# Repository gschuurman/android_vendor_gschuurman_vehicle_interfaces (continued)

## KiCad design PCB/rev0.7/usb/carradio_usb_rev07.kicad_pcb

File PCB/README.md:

# Peripheral board (mainboard)

This is the board that connects the VIM3 and the Raspberry Pi Pico 2 (vehicle MCU, firmware in `../mcu`)
to the car through the ISO 10487 harness. It also carries the audio DACs, GNSS, the display adapter, the
USB hub and the 5V supply.

- `rev0.7/` is the newest set of modules: the audio module with the car mic input (`audio/`, 2x PCM5102A + PCM1808),
  the USB module and the camera capture module (`capture_1cam/`, `capture_2cam/`). The main and GNSS boards stay at rev 0.6.
  Each folder has a README with the ordering and soldering notes.
- `rev0.6/` is the built and bench-tested main board, USB module and GNSS module, plus `stencil_jig/`.
- `rev0.5/` and `rev0.4/` are the earlier split versions (main board plus plug-in modules).
- `rev0.3/` is the single board with the RP2350B chip on it instead of the Pico 2 module.
  Read `DESIGN_rev03.md` for the changes, the 48-GPIO map and the RP2350-E9 check.
- `rev0.2/` is the Pico 2 version, and its documents still describe everything rev 0.3 didn't change.
  Start with `PCB_SUMMARY_rev02.md`, then read:
  - `DESIGN_rev02.md` for the pin map and design notes
  - `DESIGN_REVIEW_rev02.md` for the design check and layout rules
  - `ORDERING_rev02.md` for LCSC parts, cost and what to check before ordering
- `rev0.1/` is the first draft, kept for reference.
- `AUDIO.md` is the audio output plan.

The schematics are generated KiCad 7 files, for import into EasyEDA Pro. To regenerate one, run
`python3 gen3.py` inside `rev0.3/` (or `gen2.py` inside `rev0.2/`).

Rev 0.3 and later are laid out in KiCad (open with KiCad 10).

## Bring-up wizards

Each board of rev 0.6 and rev 0.7 has a step-by-step bench wizard (`WIZARD.html`) next to its design. See `wizard/README.md`.

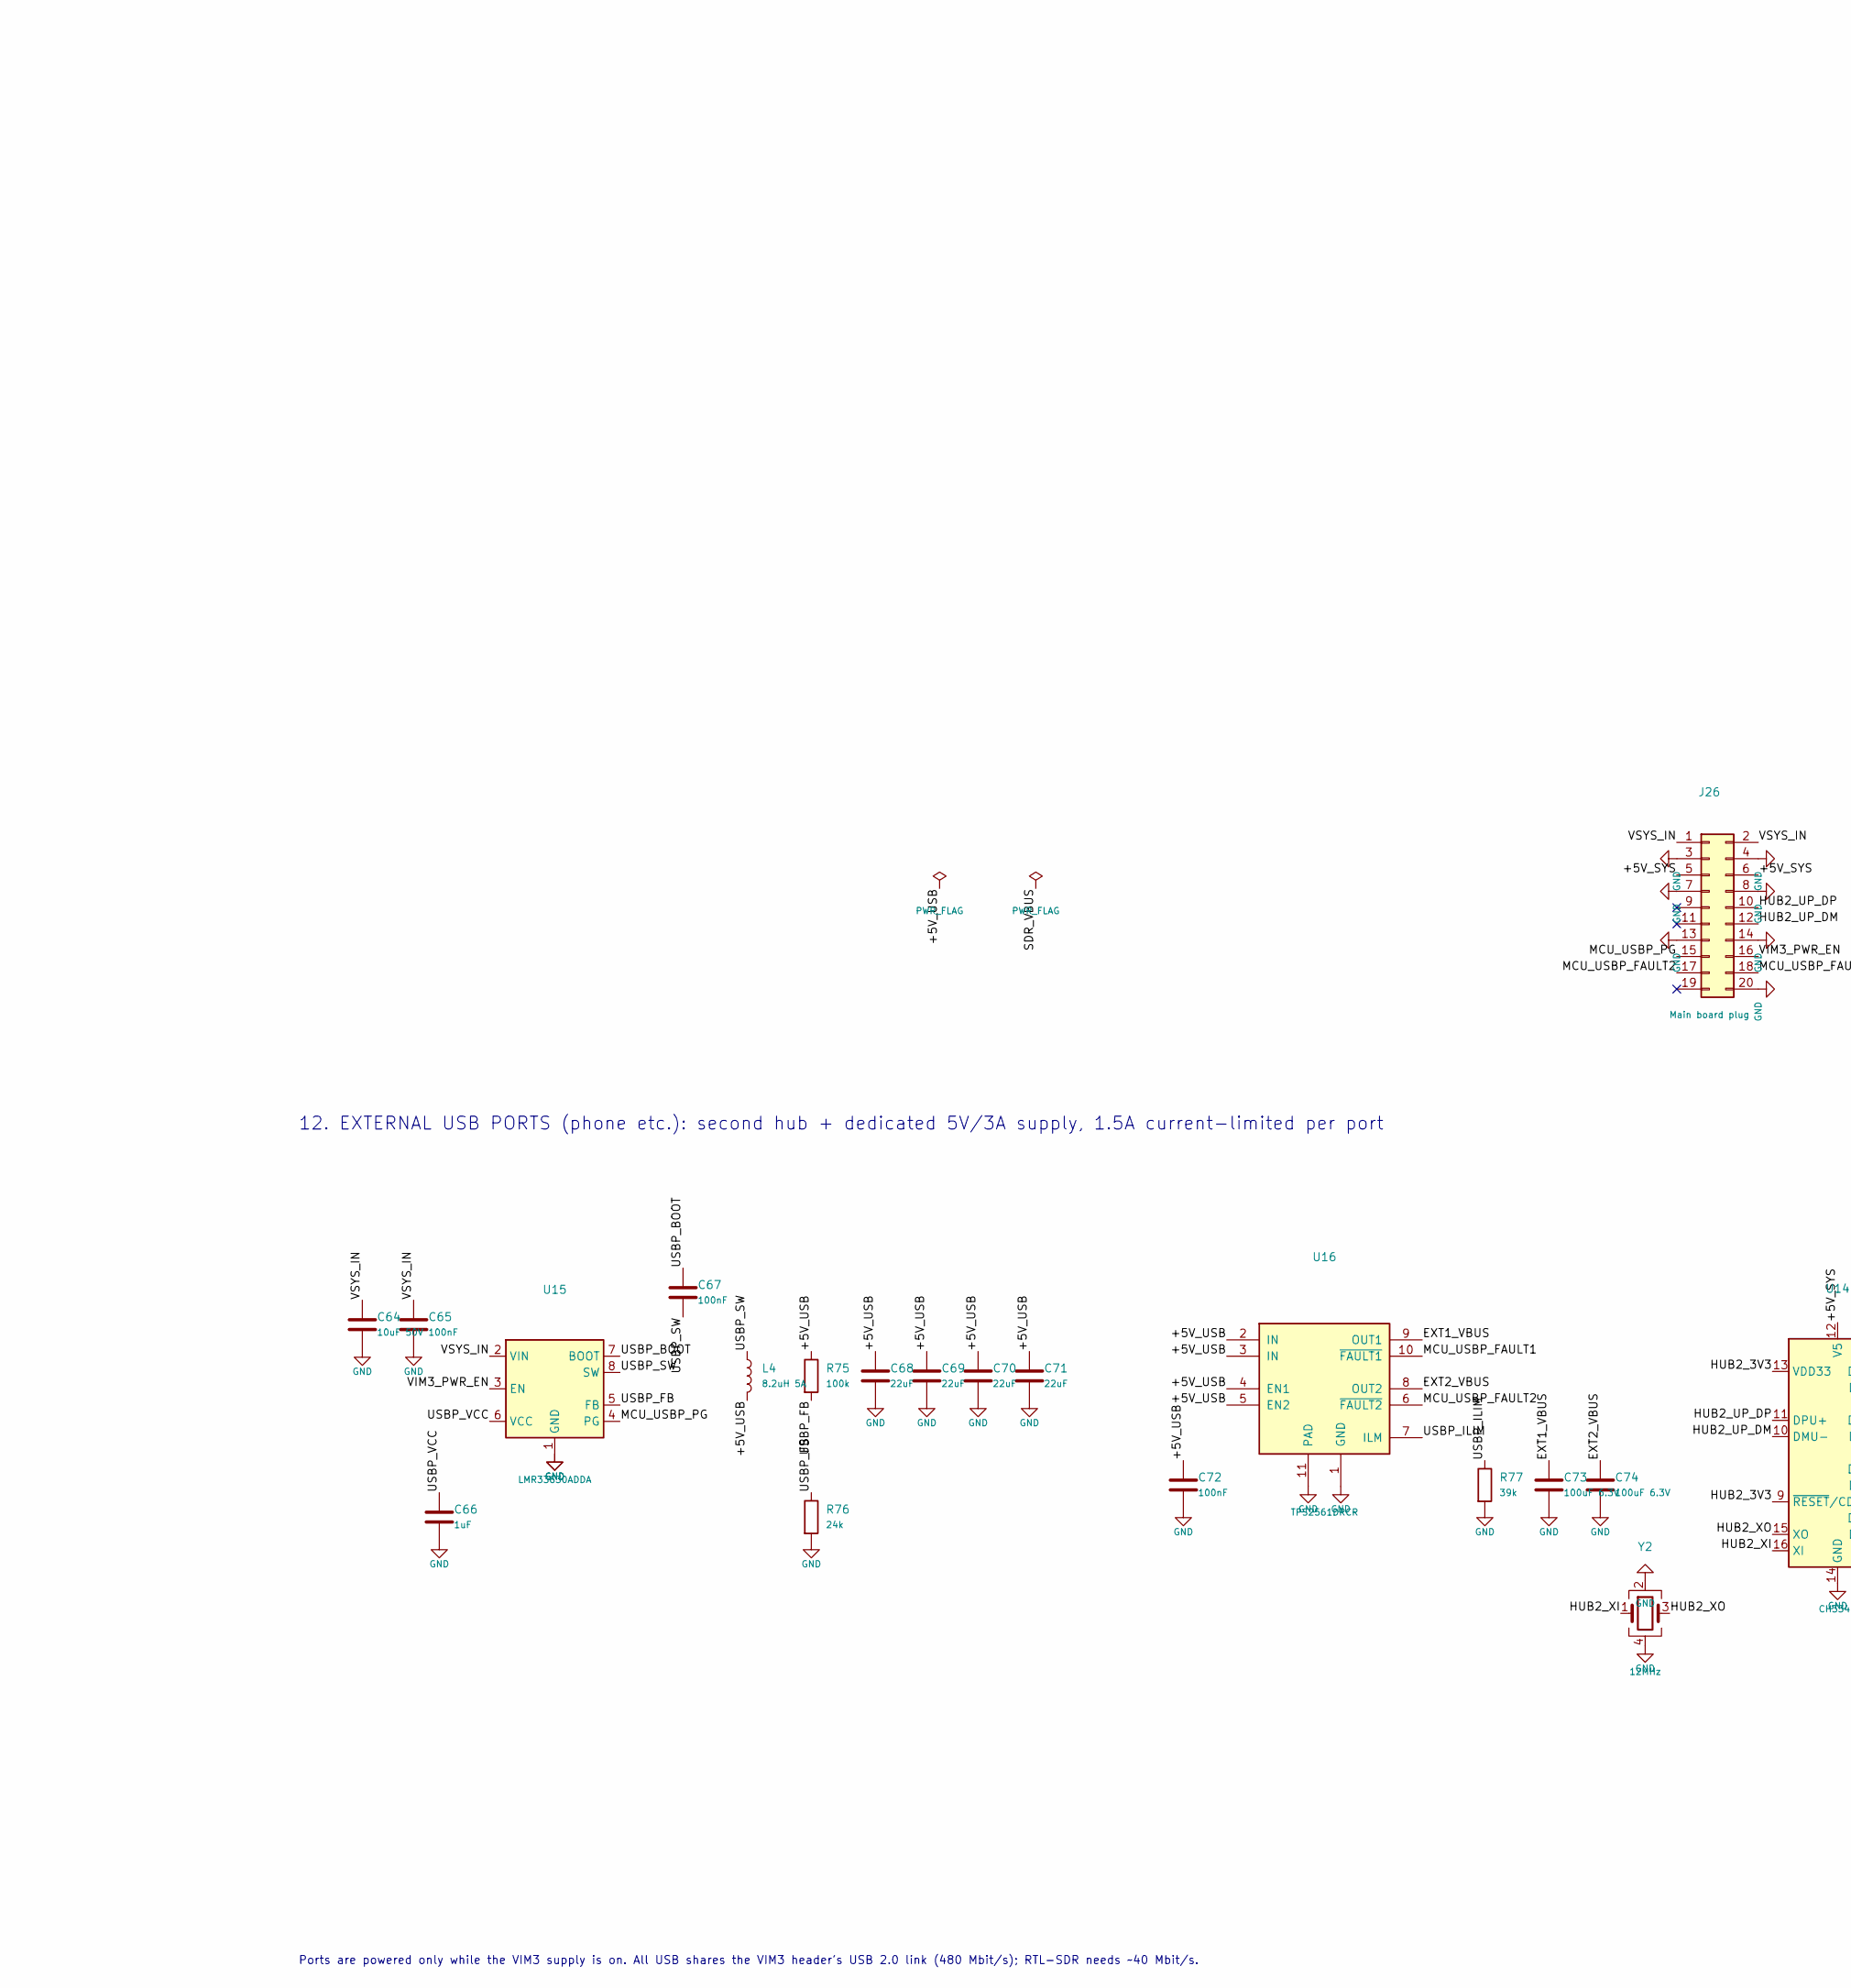
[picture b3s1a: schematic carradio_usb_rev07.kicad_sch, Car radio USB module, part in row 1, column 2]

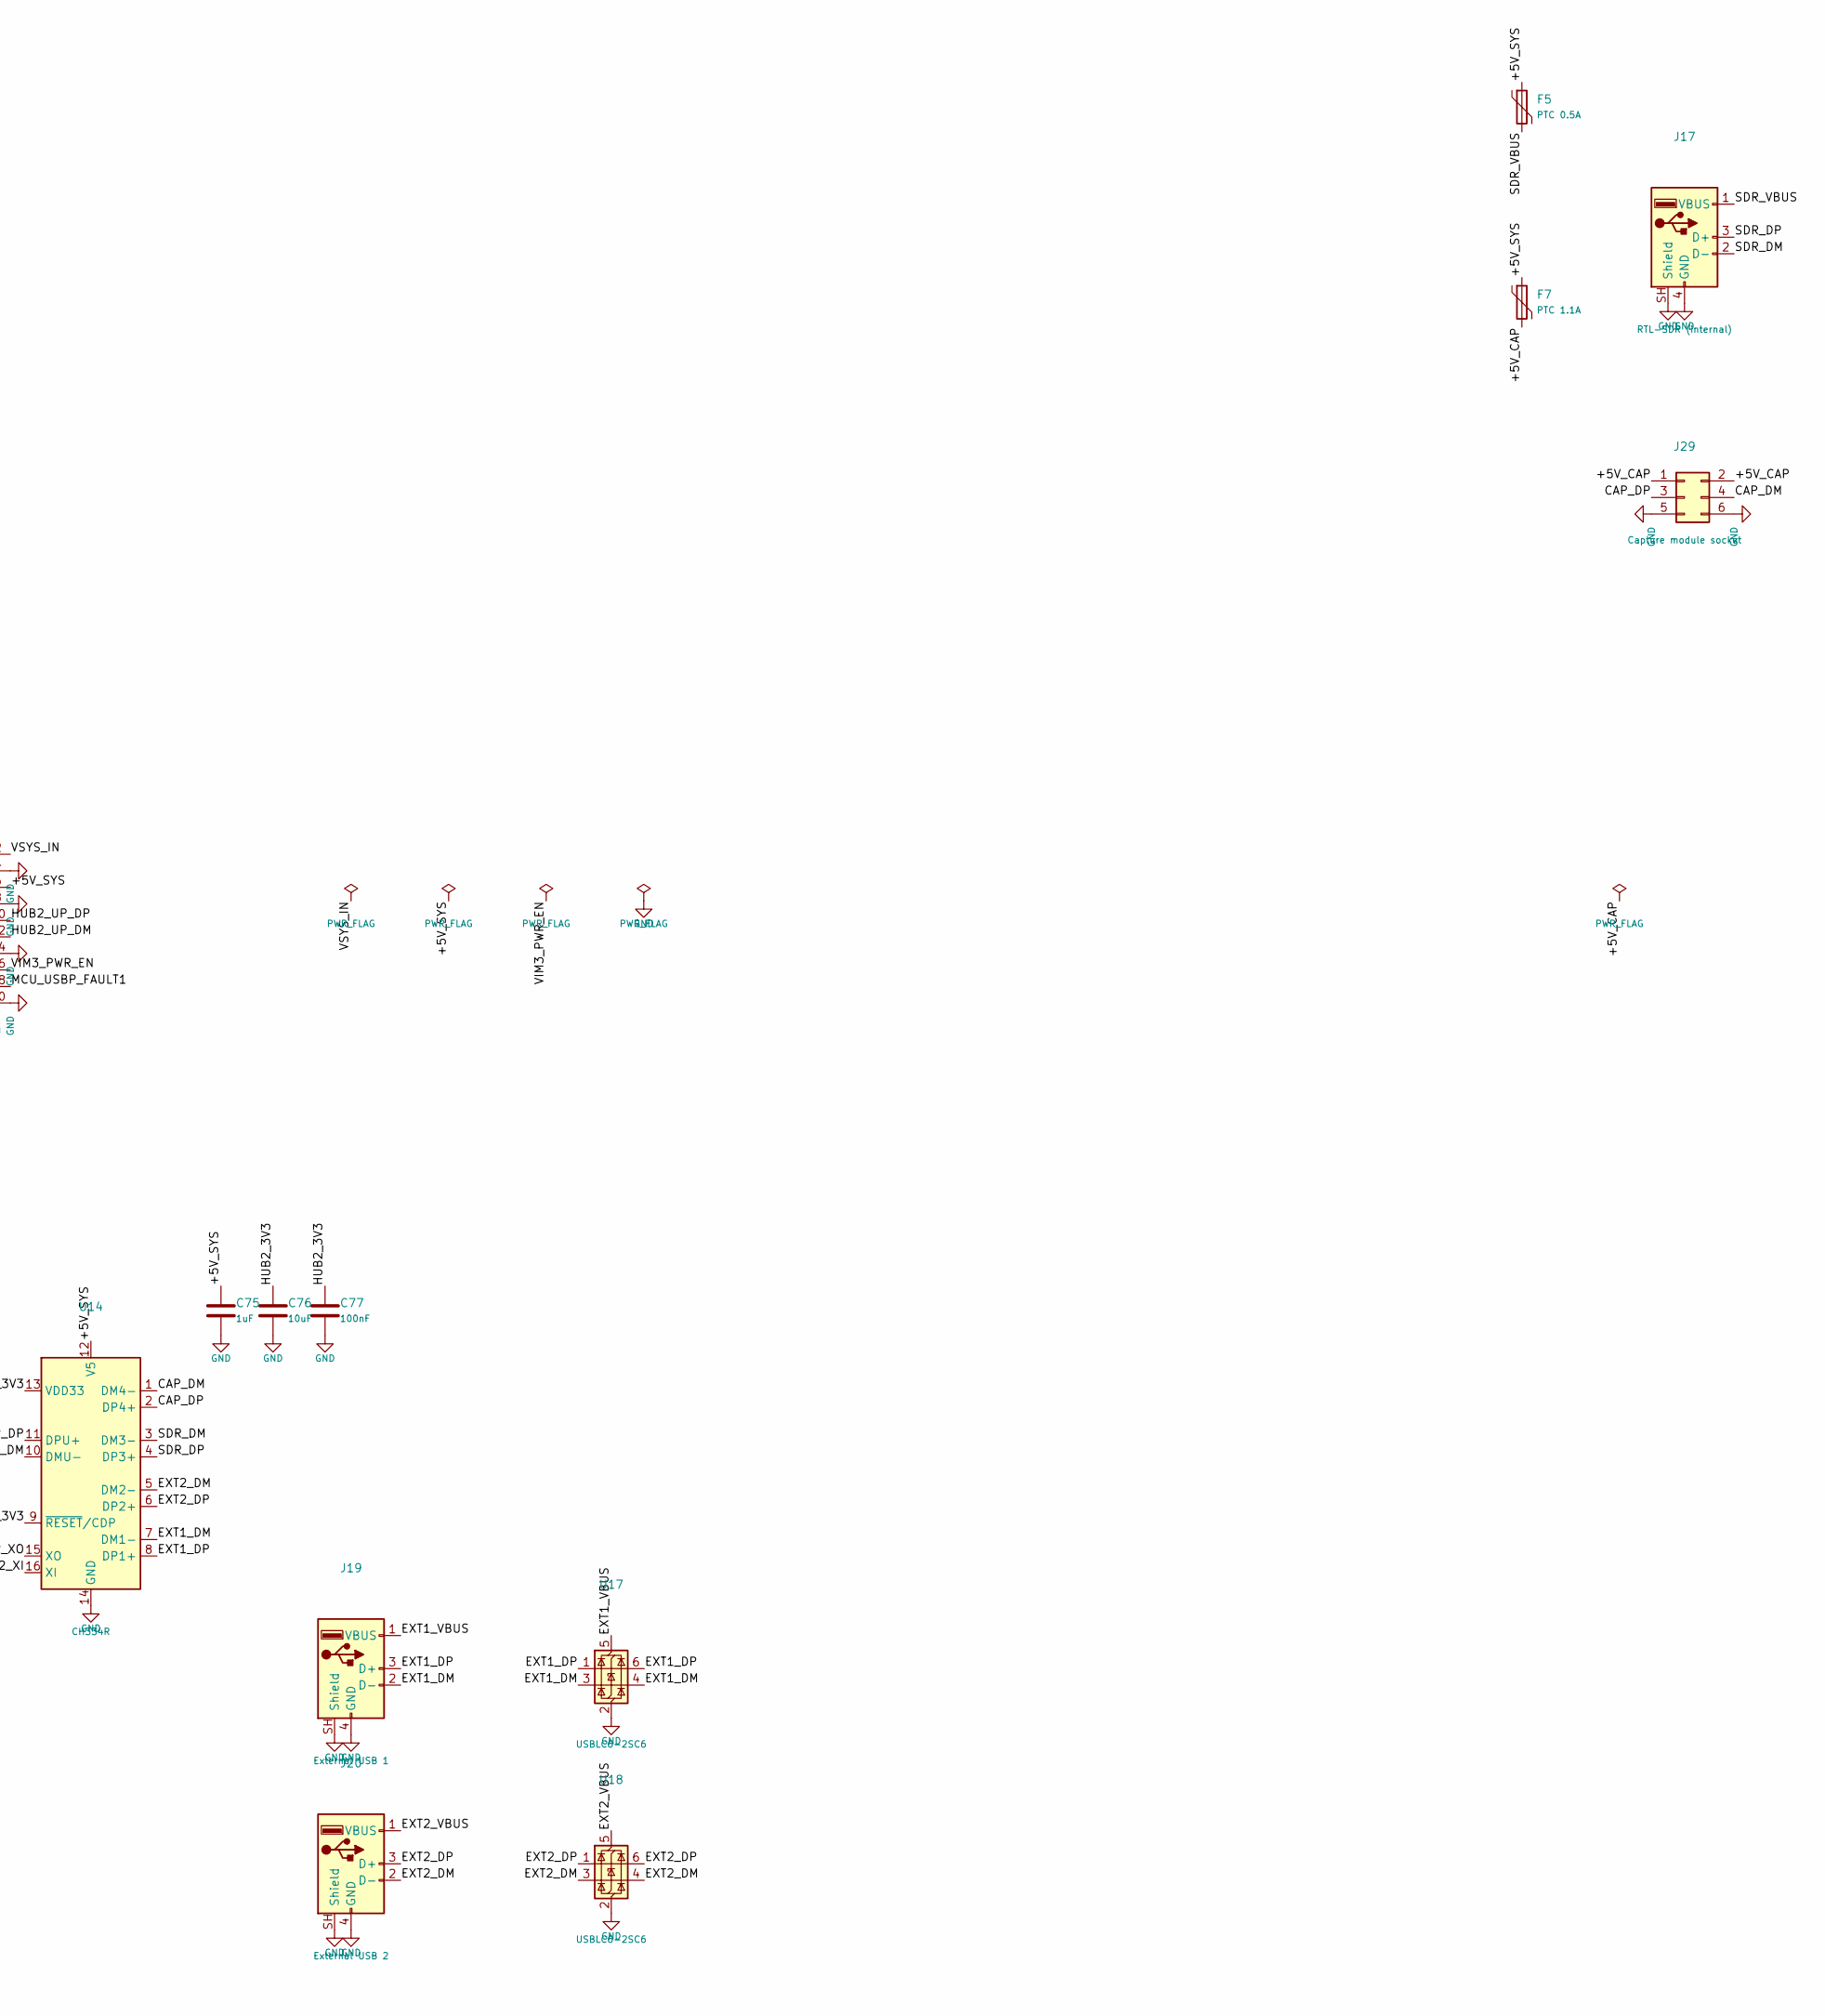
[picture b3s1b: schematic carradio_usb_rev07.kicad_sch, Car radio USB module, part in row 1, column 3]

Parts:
C64: 10uF 50V; C_1206_3216Metric; MPN 1206 10uF 50V X5R (Murata GRM31CR61H106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; LCSC C77092
C65, C67, C72, C77: 100nF; C_0603_1608Metric; MPN 0603 100nF 50V X7R; LCSC C14663
C66, C75: 1uF; C_0603_1608Metric; MPN 0603 1uF 50V X5R (Murata GRM188R61H105K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; LCSC C77386
C68, C69, C70, C71: 22uF; C_0805_2012Metric; MPN 0805 22uF 25V X5R; LCSC C45783
C73, C74: 100uF 6.3V; C_1206_3216Metric; MPN 1206 100uF 6.3V X5R; LCSC C15008
C76: 10uF; C_0805_2012Metric; MPN 0805 10uF 25V X5R; LCSC C15850
F5: PTC 0.5A; Fuse_1206_3216Metric; MPN Bourns MF-NSMF050-2; LCSC C75464
F7: PTC 1.1A; Fuse_1206_3216Metric; MPN Bourns MF-NSMF110-2; LCSC C89654
J17: RTL-SDR (internal); USB_A_Molex_67643_Horizontal; MPN Molex 67643-0910 USB-A; LCSC C2798029
J19: External USB 1; USB_A_Molex_67643_Horizontal; MPN Molex 67643-0910 USB-A; LCSC C2798029
J20: External USB 2; USB_A_Molex_67643_Horizontal; MPN Molex 67643-0910 USB-A; LCSC C2798029
J26: Main board plug; PinHeader_2x10_P2.54mm_Vertical; MPN ZHOURI 2.54-2*10 male pin header; LCSC C5116480
J29: Capture module socket; PinSocket_2x03_P2.54mm_Vertical; MPN CJT A2541HWV-2x3P 2x3 2.54mm female soc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; LCSC C239343
L4: 8.2uH 5A; L_Coilcraft_XAL6060-XXX; MPN Coilcraft XAL6060-822MEC 8.2uH Isat 8.4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; LCSC C19191627
R75: 100k; R_0603_1608Metric; MPN 0603 100k 1%; LCSC C25803
R76: 24k; R_0603_1608Metric; MPN 0603 24k 1%; LCSC C23352
R77: 39k; R_0603_1608Metric; MPN 0603 39k 1%; LCSC C23153
U14: CH334R; QSOP-16_3.9x4.9mm_P0.635mm; MPN WCH CH334R 4-port USB 2.0 hub, QSOP-16; LCSC C4154405
U15: LMR33630ADDA; TI_SO-PowerPAD-8_ThermalVias; MPN TI LMR33630ADDAR 36V 3A buck, 400 kHz; LCSC C841384
U16: TPS2561DRCR; VSON-10-1EP_3x3mm_P0.5mm_EP1.65x2.4mm; MPN TI TPS2561DRCR dual 2.8A USB power swit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; LCSC C140303
U17, U18: USBLC6-2SC6; SOT-23-6; MPN ST USBLC6-2SC6; LCSC C7519
Y2: 12MHz; Crystal_SMD_3225-4Pin_3.2x2.5mm; MPN YXC X322512MSB4SI 12MHz; LCSC C9002

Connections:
/+5V_CAP: F7.2, J29.1, J29.2
/+5V_SYS: C75.1, F5.1, F7.1, J26.5, J26.6, U14.12 (V5)
/+5V_USB: C68.1, C69.1, C70.1, C71.1, C72.1, L4.2, R75.1, U16.2 (IN), U16.3 (IN), U16.4 (EN1), U16.5 (EN2)
/CAP_DM: J29.4, U14.1 (DM4-)
/CAP_DP: J29.3, U14.2 (DP4+)
/EXT1_DM: J19.2 (D-), U14.7 (DM1-), U17.3 (I/O2), U17.4 (I/O2)
/EXT1_DP: J19.3 (D+), U14.8 (DP1+), U17.1 (I/O1), U17.6 (I/O1)
/EXT1_VBUS: C73.1, J19.1 (VBUS), U16.9 (OUT1), U17.5 (VBUS)
/EXT2_DM: J20.2 (D-), U14.5 (DM2-), U18.3 (I/O2), U18.4 (I/O2)
/EXT2_DP: J20.3 (D+), U14.6 (DP2+), U18.1 (I/O1), U18.6 (I/O1)
/EXT2_VBUS: C74.1, J20.1 (VBUS), U16.8 (OUT2), U18.5 (VBUS)
/HUB2_3V3: C76.1, C77.1, U14.9 (~RESET/CDP), U14.13 (VDD33)
/HUB2_UP_DM: J26.12, U14.10 (DMU-)
/HUB2_UP_DP: J26.10, U14.11 (DPU+)
/HUB2_XI: U14.16 (XI), Y2.1
/HUB2_XO: U14.15 (XO), Y2.3
/MCU_USBP_FAULT1: J26.18, U16.10 (~FAULT1)
/MCU_USBP_FAULT2: J26.17, U16.6 (~FAULT2)
/MCU_USBP_PG: J26.15, U15.4 (PG)
/SDR_DM: J17.2 (D-), U14.3 (DM3-)
/SDR_DP: J17.3 (D+), U14.4 (DP3+)
/SDR_VBUS: F5.2, J17.1 (VBUS)
/USBP_BOOT: C67.1, U15.7 (BOOT)
/USBP_FB: R75.2, R76.1, U15.5 (FB)
/USBP_ILIM: R77.1, U16.7 (ILM)
/USBP_SW: C67.2, L4.1, U15.8 (SW)
/USBP_VCC: C66.1, U15.6 (VCC)
/VIM3_PWR_EN: J26.16, U15.3 (EN)
/VSYS_IN: C64.1, C65.1, J26.1, J26.2, U15.2 (VIN)
GND: C64.2, C65.2, C66.2, C68.2, C69.2, C70.2, C71.2, C72.2, C73.2, C74.2, C75.2, C76.2, C77.2, J17.4 (GND), J17.SH (Shield), J19.4 (GND), J19.SH (Shield), J20.4 (GND), J20.SH (Shield), J26.3, J26.4, J26.7, J26.8, J26.13, J26.14, J26.20, J29.5, J29.6, R76.2, R77.2, U14.14 (GND), U15.1 (GND), U15.9 (GND), U16.1 (GND), U16.11 (PAD), U17.2 (GND), U18.2 (GND), Y2.2, Y2.4; also elsewhere on the board

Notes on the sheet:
12. EXTERNAL USB PORTS (phone etc.): second hub + dedicated 5V/3A supply, 1.5A current-limited per port
Ports are powered only while the VIM3 supply is on. All USB shares the VIM3 header's USB 2.0 link (480 Mbit/s); RTL-SDR needs ~40 Mbit/s.
Car radio USB module rev 0.7 - phone ports, hub 2, their 5V/3A supply, the RTL-SDR socket and the capture module socket (J29); plugs onto the peripheral board (J26 -> J25). Generated by gen4.py usb.

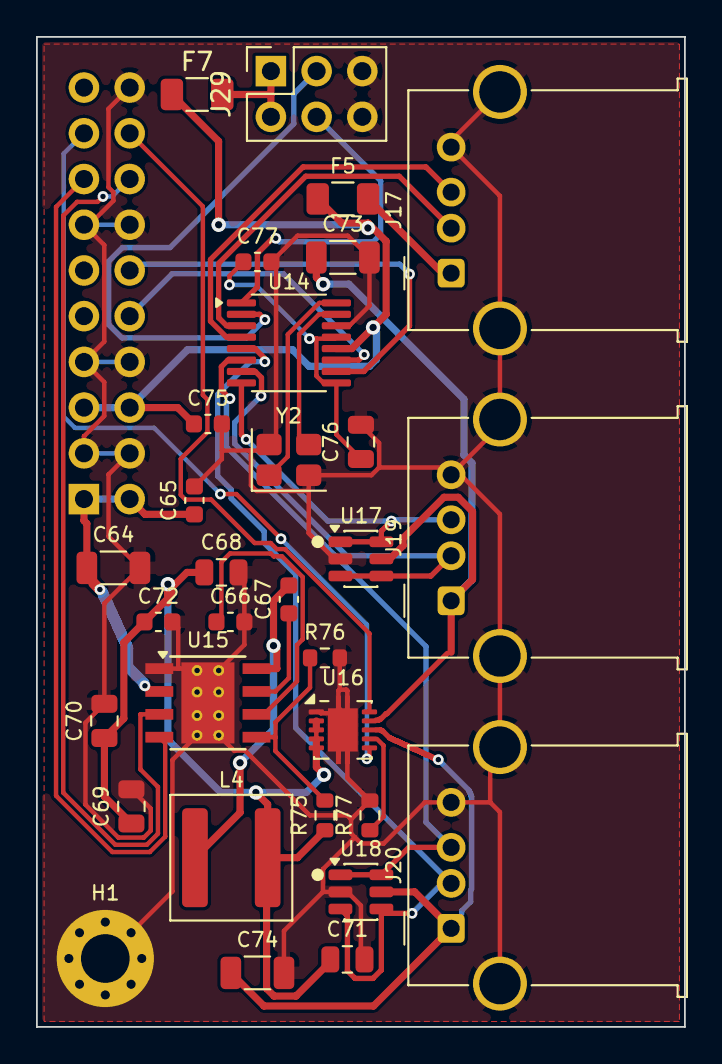
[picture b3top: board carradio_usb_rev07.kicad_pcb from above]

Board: 2 copper layers, 36.0 x 55.0 mm, 32 parts (1 on the bottom side), 30 nets.

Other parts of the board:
H1: M2.5 standoff; MountingHole_2.7mm_M2.5_Pad_Via

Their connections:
GND: H1.1; also elsewhere on the board
